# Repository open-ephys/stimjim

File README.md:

Stimjim - a flexible, precise, and inexpensive open-source stimulator
-------------------------------
Stimjim is a current and voltage stimulator for stimulating neural tissue (as with stimulating electrodes). 

# Specifications:

 - Two independently-controllable output channels, each with both current and voltage output modes
 - Output range in current mode: -3.33mA to +3.33mA. 
 - Output range in voltage mode: -15V to 15V.
 - Pulse width down to 0.02 ms (as configured with default firmware)
 - Compliance voltage is +-13.7V in current mode (+/-3.33uA output possible for resistances up to 4k, +-137uA possible for resistances up to 100k)
 - Powered by USB
 - Channels are isolated from power supply and from each other.
 - Onboard ADC measurement of actual output current or voltage
 
# Building your own Stimjim:

Here are the steps to build your very own Stimjim box. 

### Option 1: Assemble (solder components onto) the board yourself.

1. Order printed circuit boards (PCBs) for the [main board](./PCB/stimjimFabricationFiles_v0.181.zip) (4-layer, 129x79.5 mm, otherwise standard order parameters) and the [enclosure front and back panels](./PCB/stimjimPanelFabricationFiles_v0.18.zip) (1-layer, 2 designs, total size 140x71 mm) from [JLCPCB](https://jlcpcb.com/), [Seeedstudio](https://www.seeedstudio.com/fusion_pcb.html) or any other PCB manufacturer. Note that for the panels, the PCB manufacturer may alert you to the fact that there is no exposed copper. This is correct, there should be a copper layer entirely covered by soldermask.
2. Order [components](./stimjim_BOM.xlsx) (entirely from [Digikey](https://www.digikey.com/)).
3. Solder components onto the PCB, using the [schematic](./schematic.pdf) and [layout](./pcb.pdf) files for reference. This may take a few hours, depending on your soldering experience and capability. I typically use a pair of good tweezers, leaded solder paste, and a soldering iron, although a reflow oven also will work as well and may be easier.

### Option 2: Use [SeeedStudio's assembly service](https://www.seeedstudio.com/fusion_pcb.html). 
Recent estimate is about $800 for two assembled boards, plus another roughly $100 for the enclosure and panels. Thanks to Vincent Prevosto for trying this out and submitting these instructions!

1.  The main board PCB and components can be ordered and assembled together on SeeedStudio.
    To order assembled boards, go to [https://www.seeedstudio.com/fusion_pcb.html](https://www.seeedstudio.com/fusion_pcb.html).
   
    *   Click on **Add Gerber Files** and upload [the main board Gerber files](./PCB/stimjimFabricationFiles_v0.181.zip). 
        Make sure to select 4 layers and enter correct dimensions (129x79.5 mm). 
        Select PCB quantity (minimum 5).
    *   Move now to the **PCB Assembly** section.
    *   Click on **Add Assembly Drawing & Pick and Place File** and upload the [zip file containing pdf assembly files and position files](./PCB/stimjim_SeeedStudioAssembly_PickAndPlace.zip).
    *   Select the requested PCB assembly quantity (tested with 2 for $780 USD in late 2019).
    *   Click on **Add BOM File** and upload the [Seeedstudio-formatted Bill of Materials](./PCB/stimjim_SeeedStudioAssembly_BOM.xlsx). The service will check parts availability. Seeedstudio may not be able to provide an instant quote, but they should send you one within a day.
    *   Seeedstudio-assembled Stimjims have been successfully tested by one user, but you have the option to have SeeedStudio test the assembly as well.
   
2. Order the [front and back panels for the enclosure](./PCB/stimjimPanelFabricationFiles_v0.18.zip) (1-layer, 2 designs, total size 140x71 mm) from [Seeedstudio](https://www.seeedstudio.com/fusion_pcb.html), [JLCPCB](https://jlcpcb.com/) or any other PCB company you like.
3. Order the enclosure itself (see the line "enclosure" in the [Bill of materials](./stimjim_BOM.xlsx)) from [Digikey](https://www.digikey.com/).

### Continuing from either option 1 or 2:

4.  Put the main board inside the enclosure (bottom slot), and screw the panels onto the front and back of the enclosure. 
5.  Connect the Stimjim to the computer via USB. Compile and download the [firmware](./stimjimPulser/) onto the Teensy, using the [Arduino IDE](https://www.arduino.cc/en/main/software) with [Teensyduino](https://www.pjrc.com/teensy/td_download.html) installed (or write your own!). Before compiling stimjimPulser.ino, You will need to install the Stimjim library by copying the [stimjim library folder](./lib/) to the appropriate arduino "libraries" folder on your computer. On Windows, this is typically My Documents/Arduino/libraries and on linux it is typically ~/Arduino/libraries. 
6.  Upon bootup, Stimjim should self-report (via the serial connection, visible using the "Serial Monitor" tool in the Arduino IDE) on a handful of calibration routines it runs. Example output looks as follows:

	    Booting StimJim on Teensy 3.5!
	    Initializing inputs...
	    ADC offsets (+-2.5V): -11.030000, -11.150000
	    ADC offsets (+-10V): -10.220000, -10.340000
	    current offsets: 11, 8
	    voltage offsets: 0, 0
	    Ready to go!
	   
	The ADC offsets indicate the ADC reading (in ADC units, 2.4mV per ADC unit) from the output when the output is grounded, for channels 0 and 1, respectively. The ADC typically has a small but nonzero "Zero offset error" which is the reading when it should be reading exactly 0V. Stimjim measures this error (with two different range settings) and corrects all subsequent readings. We typically see values less than 20 - a value of +-4096 indicates some sort of problem with the board.
	
	Current offsets are the raw value of the DAC output (-32768 to 32767) that yields the current reading closest to 0uA. This offset is also used in subsequent stimulation to avoid any small but consistent DC current during pulses.

# Getting started using Stimjim:

To generate a pulse train, you first need to send a serial command, terminated by a newline (\n) in order to define a PulseTrain. An example command would be:

    S0,0,1,2000,1000000; 100,0,150; -100,-100,200
   
The "S" is to *s*pecify the parameters of a pulse train, and the zero immediately following the S implies that we are going to set parameters for PulseTrain 0. The code provided here allows Stimjim to store 100 different PulseTrain parameter sets. If any comma- and semicolon-separated numbers appear following the S, they are the pulse train parameters. A command that simply consists of "S0" will result in simply printing out the current parameters of PulseTrain 0. 

Once a PulseTrain is defined, to run it you would send a command of the form:

    T0

This tells Stimjim to start running PulseTrain 0. If we had parameterized PulseTrain #3, we could just as easily run PulseTrain #3 with the command "T3".

##  Parameterization 

The numbers that come after an "S" indicate parameters as denoted below:

1. [PulseTrain number], 
2. [output 0 mode],
3. [output 1 mode],
4. [period],
5. [duration];
6. [mV or uA for stage 0 output 0],
7. [mV or uA for stage 0 output 1],
8. [stage 0 duration (us)]; 
9. [mV or uA for stage 1 output 0],
10. [mV or uA for stage 1 output 1],
11. [stage 1 duration (us)];
12. (etc for additional stages, up to 10 total stages).

After the "S", the first parameter is the number of the PulseTrain that we are defining. The next two parameters are the modes of each output channels. Modes are as follows:

 - 0 = Voltage output
 - 1 = Current output
 - 2 = Output is disconnected
 - 3 = Output is grounded

Our example command above was: 
   
    S0,0,1,2000,1000000; 100,0,150; -100,-100,200
   
In this example, output 0 is generating a voltage output (mode 0), and output 1 is generating a current output (mode 1). To specify that a channel should not output anything during a pulse train, set the mode to 3 (ground).  

The fourth parameter is the _period_ of the pulse train. In this example, pulses are delivered every 2000 us (2 ms).

The fifth parameter is the _duration_ of the pulse train, in microseconds. In the example, the pulse train lasts for one second (1000000 microseconds).

Parameters after the 5th come in sets of 3, and describe a "stage" of a pulse in the train.  The first two parameters are the amplitude (in mV or uA, depending on whether the output is voltage or current) of each channel during that stage, and the third is the duration (in microseconds) of that stage. Note that a semi-colon is before the beginning of each set of 3, and the three parameters themselves are separated from each other by commas.

In the example given above, there are two stages to each pulse. In the first, channel 0 outputs 100mV, channel 1 outputs nothing, and that lasts for 150 usec. Then channel 0 switches to outputting -100mV, and channel 2 outputs -100uA for 200 usec. 

## Triggering
Stimjim can utilize trigger signals from its BNC inputs. To make a rising edge on input 0 trigger PulseTrain 1, send the command

	R0,1

To make a rising edge on input 1 trigger PulseTrain 2

	R1,2
	
And finally, to make a falling edge on input 1 trigger PulseTrain 2:

	R1,2,1

The final argument for the R command is optional, and defaults to 0 (rising edge).

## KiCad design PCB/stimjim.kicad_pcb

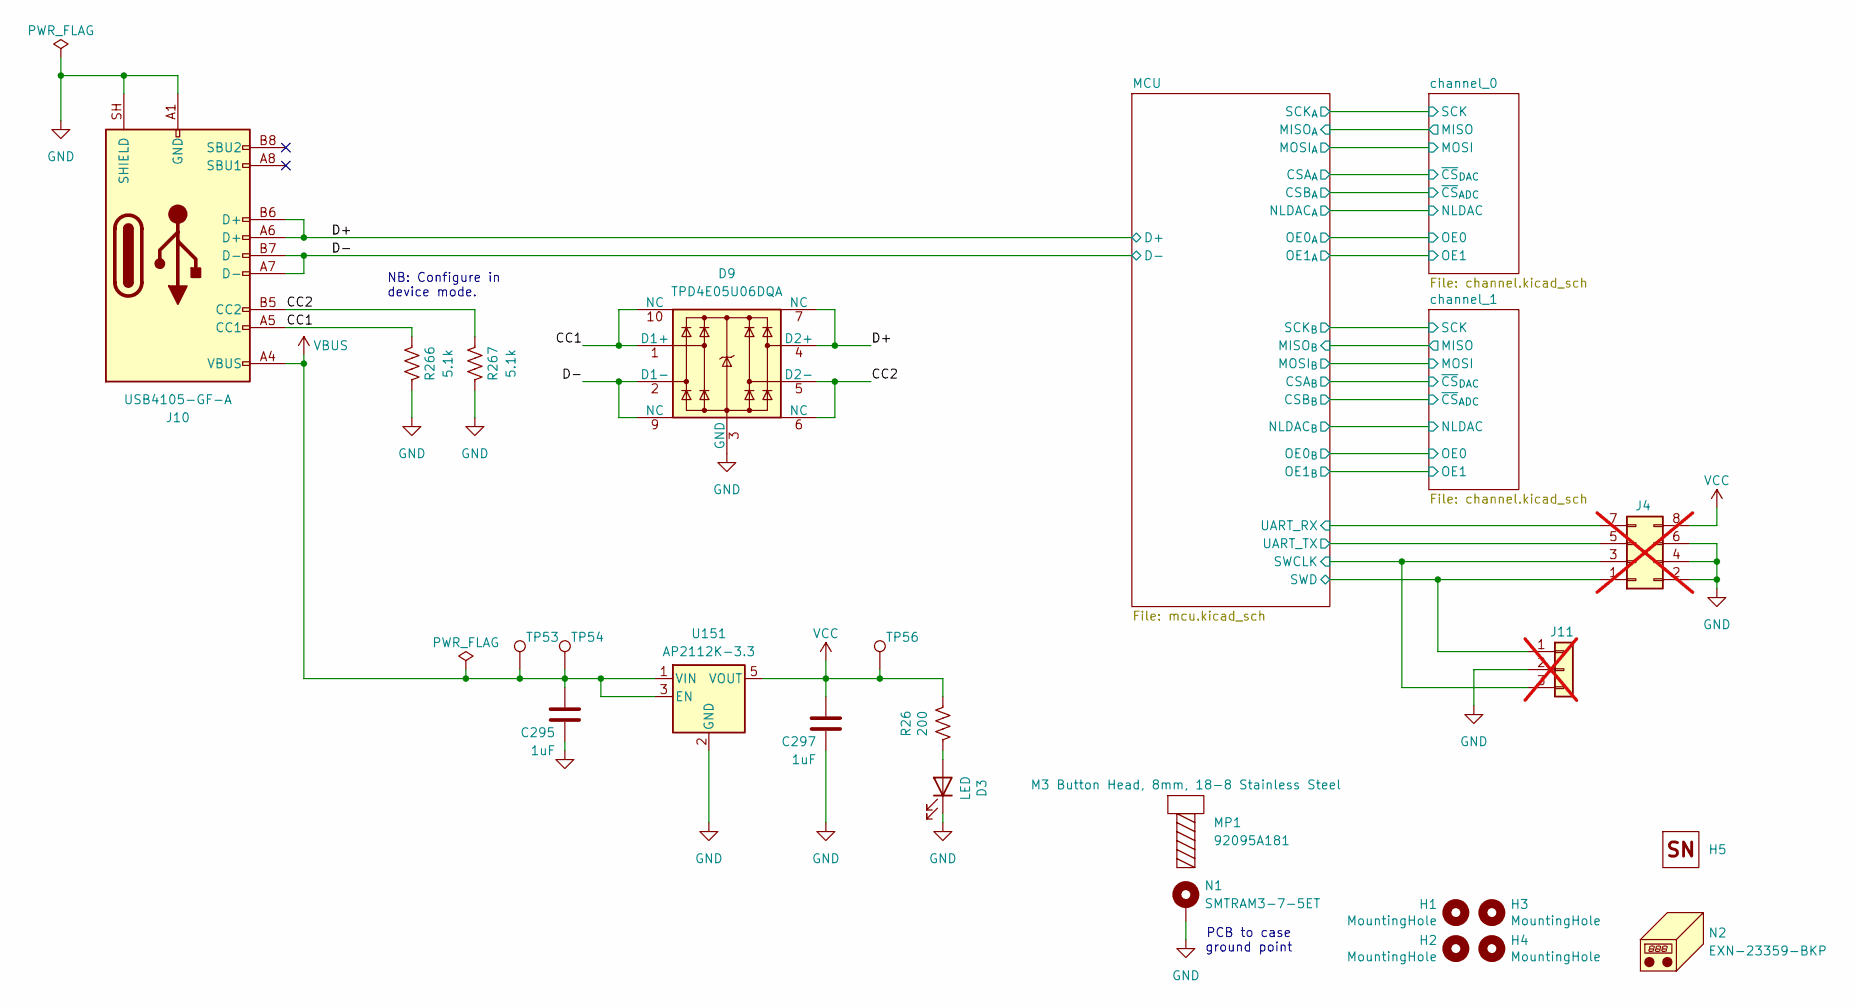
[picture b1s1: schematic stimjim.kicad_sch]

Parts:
C295, C297: 1uF; C_0603_1608Metric; Voltage 25V; MPN CL10A105KA8NNNC
D3: LED; LUMEX_SSF-LHXH100GD-01; MPN SSF-LXH100GD-01
D9: TPD4E05U06DQA; USON-10_2.5x1.0mm_P0.5mm; MPN TPD4E05U06DQAR
H1, H2, H3, H4: MountingHole; MountingHole_4.3mm_M4
H5: OEPS_SN-STICKER-8x20mm
J4: 10129383-910002ALF; PinHeader_2x04_P2.54mm_Vertical_SMD; MPN 10129383-910002ALF; not fitted
J10: USB4105-GF-A; USB_C_Receptacle_GCT_USB4105-xx-A_16P_TopMnt_Horizontal; MPN USB4105-GF-A
J11: BM03B-SRSS-TB; JST_SH_BM03B-SRSS-TB_1x03-1MP_P1.00mm_Vertical; MPN BM03B-SRSS-TB; not fitted
MP1: 92095A181
N1: SMTRAM3-7-5ET; SMTRA_M3-7-5ET; MPN SMTRAM3-7-5ET
N2: EXN-23359-BKP; MPN EXN-23359-SVP
R26: 200; R_0603_1608Metric; MPN RC0603FR-07200RL
R266, R267: 5.1k; R_0402_1005Metric; Tolerance 1%; MPN ERJ-2RKF5101X
TP53, TP54: GND; TestPoint_Pad_D2.0mm
TP56: VCC; TestPoint_Pad_D2.0mm
U151: AP2112K-3.3; SOT-23-5; MPN AP2112K-3.3TRG1

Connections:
/CC1: D9.1 (D1+), D9.10 (NC), J10.A5 (CC1), R266.1
/CC2: D9.5 (D2-), D9.6 (NC), J10.B5 (CC2), R267.1
/D+: D9.4 (D2+), D9.7 (NC), J10.A6 (D+), J10.B6 (D+); also elsewhere on the board
/D-: D9.2 (D1-), D9.9 (NC), J10.A7 (D-), J10.B7 (D-); also elsewhere on the board
/MCU/SWCLK: J4.3, J11.3; also elsewhere on the board
/MCU/SWD: J4.1, J11.1; also elsewhere on the board
/MCU/UART_RX: J4.7; also elsewhere on the board
/MCU/UART_TX: J4.5; also elsewhere on the board
GND: C295.2, C297.2, D3.1 (K), D9.3 (GND), D9.8 (GND), J4.2, J4.4, J4.6, J10.A1 (GND), J10.A12 (GND), J10.B1 (GND), J10.B12 (GND), J10.SH (SHIELD), J11.2, N1.1 (1_1), R266.2, R267.2, U151.2 (GND); also elsewhere on the board
unnamed: D3.2 (A), R26.2
VBUS: C295.1, J10.A4 (VBUS), J10.A9 (VBUS), J10.B4 (VBUS), J10.B9 (VBUS), TP53.1 (1_1), TP54.1 (1_1), U151.1 (VIN), U151.3 (EN); also elsewhere on the board
VCC: C297.1, J4.8, R26.1, TP56.1 (1_1), U151.5 (VOUT); also elsewhere on the board

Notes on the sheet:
NB: Configure in device mode.
PCB to case ground point

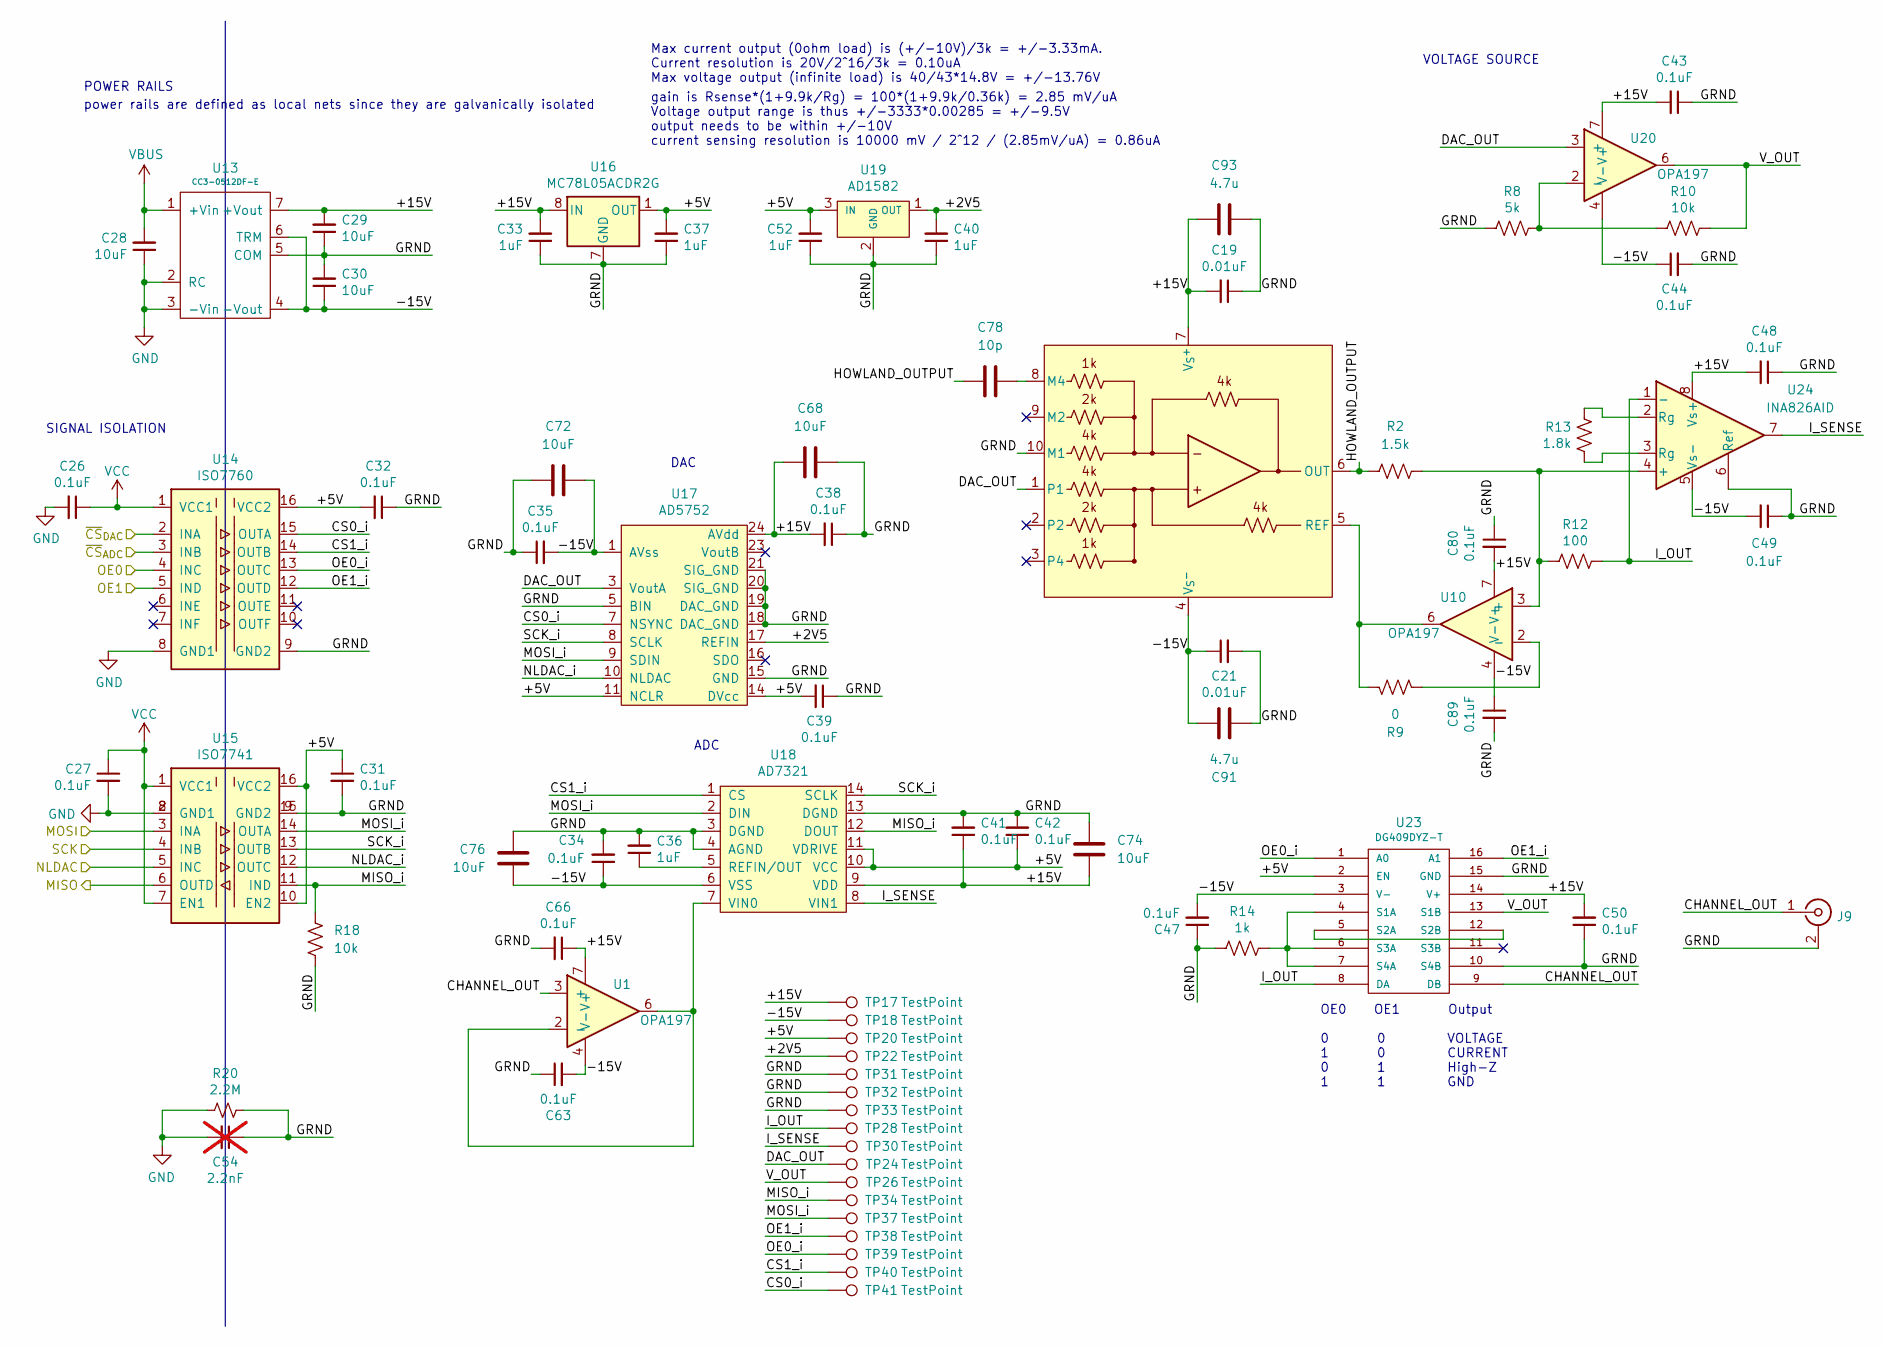
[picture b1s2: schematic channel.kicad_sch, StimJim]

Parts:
C19, C21: 0.01uF; C_0603_1608Metric; MPN C1608X7R1H103K080AA
C26, C27, C31, C32, C34, C35, C38, C39, C41, C42, C43, C44, C47, C48, C49, C50, C63, C66, C80, C89: 0.1uF; C_0603_1608Metric; MPN GRM188R72A104KA35D
C28, C29, C30: 10uF; C_1206_3216Metric_Pad1.33x1.80mm_HandSolder; Voltage 25V; MPN GRT319R6YA106KE01D
C33, C36, C37, C40, C52: 1uF; C_0603_1608Metric; Voltage 25V; MPN CL10A105KA8NNNC
C54: 2.2nF; C_1210_3225Metric_Pad1.33x2.70mm_HandSolder; MPN DNP; not fitted
C68, C72, C74, C76: 10uF; C_0603_1608Metric; MPN GRM188R6YA106MA73J
C78: 10p; C_0603_1608Metric; MPN C0603C100J5GACTU
C91, C93: 4.7u; C_0603_1608Metric; MPN GRM188R61E475KE11D
J9: 0731375003; BNC_Amphenol_B6252HB-NPP3G-50_Horizontal; MPN 0731375003
R2: 1.5k; R_0603_1608Metric; Tolerance 0.1%; MPN RG1608P-152-B-T5
R8: 5k; R_0603_1608Metric; Tolerance 0.1%; MPN RT0603BRE075KL
R9: 0; R_0603_1608Metric; MPN RCS06030000Z0EA
R10: 10k; R_0603_1608Metric; Tolerance 0.1%; MPN RG1608P-103-B-T5
R12: 100; R_0603_1608Metric; Tolerance 0.1%; MPN RG1608P-101-B-T5
R13: 1.8k; R_0603_1608Metric; Tolerance 0.1%; MPN RG1608P-182-B-T5
R14: 1k; R_0603_1608Metric; Tolerance 1%; MPN RG1608P-102-B-T5
R18: 10k; R_0603_1608Metric; MPN RC0603FR-0710KL
R20: 2.2M; R_1210_3225Metric_Pad1.30x2.65mm_HandSolder; MPN CRGCQ1210J2M2
TP17, TP18, TP20, TP22: TestPoint; TestPoint_THTPad_1.0x1.0mm_Drill0.5mm
TP24, TP26, TP28, TP30, TP31, TP32, TP33, TP34, TP37, TP38, TP39, TP40, TP41: TestPoint; TestPoint_THTPad_D1.0mm_Drill0.5mm
U1, U10, U20: OPA197; SOIC-8_3.9x4.9mm_P1.27mm; MPN OPA197IDR
U13: CC3-0512DF-E; MPN CC3-0512DF-E
U14: ISO7760; SOIC-16W_7.5x10.3mm_P1.27mm; MPN ISO7760DWR
U15: ISO7741; SOIC-16W_7.5x10.3mm_P1.27mm; MPN ISO7741DWR
U16: MC78L05ACDR2G; SOIC-8_3.9x4.9mm_P1.27mm; MPN MC78L05ACDR2G
U17: AD5752; TSSOP-24_4.4x7.8mm_P0.65mm; MPN AD5752AREZ
U18: AD7321; TSSOP-14_4.4x5mm_P0.65mm; MPN AD7321BRUZ-REEL7
U19: AD1582; SOT-23; MPN AD1582ARTZ-REEL7
U23: DG409DYZ-T; SO-16_3.9x9.9mm_P1.27mm; MPN DG409DYZ-T
U24: INA826AID; SOIC-8_3.9x4.9mm_P1.27mm; MPN INA826AIDR
U27: LT1995; MSOP-10_3x3mm_P0.5mm; MPN LT1995CMS#PBF

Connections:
/MCU/CSA_{A}: U14.2 (INA); also elsewhere on the board
/MCU/CSB_{A}: U14.3 (INB); also elsewhere on the board
/MCU/MISO_{A}: U15.6 (OUTD); also elsewhere on the board
/MCU/MOSI_{A}: U15.3 (INA); also elsewhere on the board
/MCU/NLDAC_{A}: U15.5 (INC); also elsewhere on the board
/MCU/OE0_{A}: U14.4 (INC); also elsewhere on the board
/MCU/OE1_{A}: U14.5 (IND); also elsewhere on the board
/MCU/SCK_{A}: U15.4 (INB); also elsewhere on the board
/channel_0/+2V5: C40.2, TP22.1 (1_1), U17.17 (REFIN), U19.1 (OUT)
/channel_0/+5V: C31.1, C32.2, C37.2, C39.2, C42.1, C52.2, TP20.1 (1_1), U14.16 (VCC2), U15.10 (EN2), U15.16 (VCC2), U16.1 (OUT), U17.11 (NCLR), U17.14 (DVcc), U18.10 (VCC), U18.11 (VDRIVE), U19.3 (IN), U23.2 (EN)
/channel_0/+15V: C19.2, C29.2, C33.2, C38.2, C41.1, C43.2, C48.2, C50.2, C66.1, C68.1, C74.1, C80.2, C93.2, TP17.1 (1_1), U1.7 (V+), U10.7 (V+), U13.7 (+Vout), U16.8 (IN), U17.24 (AVdd), U18.9 (VDD), U20.7 (V+), U23.14 (V+), U24.8 (Vs+), U27.7 (V_{S}^{+})
/channel_0/-15V: C21.1, C30.1, C34.1, C35.2, C44.1, C47.2, C49.2, C63.2, C72.2, C76.2, C89.1, C91.2, TP18.1 (1_1), U1.4 (V-), U10.4 (V-), U13.4 (-Vout), U13.6 (TRM), U17.1 (AVss), U18.6 (VSS), U20.4 (V-), U23.3 (V-), U24.5 (Vs-), U27.4 (V_{S}^{-})
/channel_0/CHANNEL_OUT: J9.1 (In), U1.3 (+), U23.9 (DB)
/channel_0/CS0_i: TP41.1 (1_1), U14.15 (OUTA), U17.7 (NSYNC)
/channel_0/CS1_i: TP40.1 (1_1), U14.14 (OUTB), U18.1 (CS)
/channel_0/DAC_OUT: TP24.1 (1_1), U17.3 (VoutA), U20.3 (+), U27.1
/channel_0/GRND: C19.1, C21.2, C29.1, C30.2, C31.2, C32.1, C33.1, C34.2, C35.1, C36.2, C37.1, C38.1, C39.1, C40.1, C41.2, C42.2, C43.1, C44.2, C47.1, C48.1, C49.1, C50.1, C52.1, C54.1, C63.1, C66.2, C68.2, C72.1, C74.2, C76.1, C80.1, C89.2, C91.1, C93.1, J9.2 (Ext), R8.1, R14.1, R18.1, R20.1, TP31.1 (1_1), TP32.1 (1_1), TP33.1 (1_1), U13.5 (COM), U14.9 (GND2), U15.9 (GND2), U15.15 (GND2), U16.2 (GND), U16.3 (GND), U16.6 (GND), U16.7 (GND), U17.5 (BIN), U17.15 (GND), U17.18 (DAC_GND), U17.19 (DAC_GND), U17.20 (SIG_GND), U17.21 (SIG_GND), U18.3 (DGND), U18.4 (AGND), U18.13 (DGND), U19.2 (GND), U23.10 (S4B), U23.15 (GND), U24.6 (Ref), U27.10 (M1)
/channel_0/HOWLAND_OUTPUT: C78.1, R2.1, U27.6 (OUT)
/channel_0/I_OUT: R12.2, TP28.1 (1_1), U23.8 (DA), U24.1 (-)
/channel_0/I_SENSE: TP30.1 (1_1), U18.8 (VIN1), U24.7
/channel_0/MISO_i: R18.2, TP34.1 (1_1), U15.11 (IND), U18.12 (DOUT)
/channel_0/MOSI_i: TP37.1 (1_1), U15.14 (OUTA), U17.9 (SDIN), U18.2 (DIN)
/channel_0/NLDAC_i: U15.12 (OUTC), U17.10 (NLDAC)
/channel_0/OE0_i: TP39.1 (1_1), U14.13 (OUTC), U23.1 (A0)
/channel_0/OE1_i: TP38.1 (1_1), U14.12 (OUTD), U23.16 (A1)
/channel_0/SCK_i: U15.13 (OUTB), U17.8 (SCLK), U18.14 (SCLK)
/channel_0/V_OUT: R10.2, TP26.1 (1_1), U20.6, U23.13 (S1B)
GND: C26.2, C27.2, C28.1, C54.2, R20.2, U13.2 (RC), U13.3 (-Vin), U14.8 (GND1), U15.2 (GND1), U15.8 (GND1); also elsewhere on the board
unnamed: R13.1, U24.3 (Rg)
unnamed: R13.2, U24.2 (Rg)
unnamed: U1.2 (-), U1.6, U18.7 (VIN0)
unnamed: R2.2, R12.1, U10.3 (+), U24.4 (+)
unnamed: R9.2, U10.2 (-)
unnamed: C36.1, U18.5 (REFIN/OUT)
unnamed: R8.2, R10.1, U20.2 (-)
unnamed: R14.2, U23.4 (S1A), U23.6 (S3A), U23.7 (S4A)
unnamed: U23.5 (S2A), U23.12 (S2B)
unnamed: C78.2, U27.8 (M4)
unnamed: R9.1, U10.6, U27.5 (REF)
VBUS: C28.2, U13.1 (+Vin); also elsewhere on the board
VCC: C26.1, C27.1, U14.1 (VCC1), U15.1 (VCC1), U15.7 (EN1); also elsewhere on the board

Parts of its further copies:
C1, C2, C6, C7, C9, C11, C13, C14, C16, C17, C18, C20, C22, C23, C24, C25, C65, C67, C82, C90: 0.1uF; C_0603_1608Metric; MPN GRM188R72A104KA35D
C3, C4, C5: 10uF; C_1206_3216Metric_Pad1.33x1.80mm_HandSolder; Voltage 25V; MPN GRT319R6YA106KE01D
C8, C10, C12, C15, C51: 1uF; C_0603_1608Metric; Voltage 25V; MPN CL10A105KA8NNNC
C45, C46: 0.01uF; C_0603_1608Metric; MPN C1608X7R1H103K080AA
C53: 2.2nF; C_1210_3225Metric_Pad1.33x2.70mm_HandSolder; MPN DNP; not fitted
C69, C73, C75, C77: 10uF; C_0603_1608Metric; MPN GRM188R6YA106MA73J
C79: 10p; C_0603_1608Metric; MPN C0603C100J5GACTU
C92, C94: 4.7u; C_0603_1608Metric; MPN GRM188R61E475KE11D
J7: 0731375003; BNC_Amphenol_B6252HB-NPP3G-50_Horizontal; MPN 0731375003
R1: 5k; R_0603_1608Metric; Tolerance 0.1%; MPN RT0603BRE075KL
R3: 10k; R_0603_1608Metric; Tolerance 0.1%; MPN RG1608P-103-B-T5
R4: 1.5k; R_0603_1608Metric; Tolerance 0.1%; MPN RG1608P-152-B-T5
R5: 100; R_0603_1608Metric; Tolerance 0.1%; MPN RG1608P-101-B-T5
R6: 1.8k; R_0603_1608Metric; Tolerance 0.1%; MPN RG1608P-182-B-T5
R7: 1k; R_0603_1608Metric; Tolerance 1%; MPN RG1608P-102-B-T5
R11: 0; R_0603_1608Metric; MPN RCS06030000Z0EA
R17: 10k; R_0603_1608Metric; MPN RC0603FR-0710KL
R19: 2.2M; R_1210_3225Metric_Pad1.30x2.65mm_HandSolder; MPN CRGCQ1210J2M2
TP15, TP16, TP19, TP21: TestPoint; TestPoint_THTPad_1.0x1.0mm_Drill0.5mm
TP23, TP25, TP27, TP29, TP42, TP43, TP44, TP45, TP48, TP49, TP50, TP51, TP52: TestPoint; TestPoint_THTPad_D1.0mm_Drill0.5mm
U2: CC3-0512DF-E; MPN CC3-0512DF-E
U3: ISO7760; SOIC-16W_7.5x10.3mm_P1.27mm; MPN ISO7760DWR
U4: ISO7741; SOIC-16W_7.5x10.3mm_P1.27mm; MPN ISO7741DWR
U5: MC78L05ACDR2G; SOIC-8_3.9x4.9mm_P1.27mm; MPN MC78L05ACDR2G
U6: AD5752; TSSOP-24_4.4x7.8mm_P0.65mm; MPN AD5752AREZ
U7: AD7321; TSSOP-14_4.4x5mm_P0.65mm; MPN AD7321BRUZ-REEL7
U8: AD1582; SOT-23; MPN AD1582ARTZ-REEL7
U9, U21, U26: OPA197; SOIC-8_3.9x4.9mm_P1.27mm; MPN OPA197IDR
U12: DG409DYZ-T; SO-16_3.9x9.9mm_P1.27mm; MPN DG409DYZ-T
U28: LT1995; MSOP-10_3x3mm_P0.5mm; MPN LT1995CMS#PBF
U29: INA826AID; SOIC-8_3.9x4.9mm_P1.27mm; MPN INA826AIDR

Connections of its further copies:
/MCU/CSA_{B}: U3.2 (INA); also elsewhere on the board
/MCU/CSB_{B}: U3.3 (INB); also elsewhere on the board
/MCU/MISO_{B}: U4.6 (OUTD); also elsewhere on the board
/MCU/MOSI_{B}: U4.3 (INA); also elsewhere on the board
/MCU/NLDAC_{B}: U4.5 (INC); also elsewhere on the board
/MCU/OE0_{B}: U3.4 (INC); also elsewhere on the board
/MCU/OE1_{B}: U3.5 (IND); also elsewhere on the board
/MCU/SCK_{B}: U4.4 (INB); also elsewhere on the board
/channel_1/+2V5: C15.2, TP21.1 (1_1), U6.17 (REFIN), U8.1 (OUT)
/channel_1/+5V: C6.1, C7.2, C12.2, C14.2, C17.1, C51.2, TP19.1 (1_1), U3.16 (VCC2), U4.10 (EN2), U4.16 (VCC2), U5.1 (OUT), U6.11 (NCLR), U6.14 (DVcc), U7.10 (VCC), U7.11 (VDRIVE), U8.3 (IN), U12.2 (EN)
/channel_1/+15V: C4.2, C8.2, C13.2, C16.1, C18.2, C23.2, C25.2, C45.2, C67.1, C69.1, C75.1, C82.2, C94.2, TP15.1 (1_1), U2.7 (+Vout), U5.8 (IN), U6.24 (AVdd), U7.9 (VDD), U9.7 (V+), U12.14 (V+), U21.7 (V+), U26.7 (V+), U28.7 (V_{S}^{+}), U29.8 (Vs+)
/channel_1/-15V: C5.1, C9.1, C11.2, C20.1, C22.2, C24.2, C46.1, C65.2, C73.2, C77.2, C90.1, C92.2, TP16.1 (1_1), U2.4 (-Vout), U2.6 (TRM), U6.1 (AVss), U7.6 (VSS), U9.4 (V-), U12.3 (V-), U21.4 (V-), U26.4 (V-), U28.4 (V_{S}^{-}), U29.5 (Vs-)
/channel_1/CHANNEL_OUT: J7.1 (In), U12.9 (DB), U26.3 (+)
/channel_1/CS0_i: TP52.1 (1_1), U3.15 (OUTA), U6.7 (NSYNC)
/channel_1/CS1_i: TP51.1 (1_1), U3.14 (OUTB), U7.1 (CS)
/channel_1/DAC_OUT: TP23.1 (1_1), U6.3 (VoutA), U9.3 (+), U28.1
/channel_1/GRND: C4.1, C5.2, C6.2, C7.1, C8.1, C9.2, C10.2, C11.1, C12.1, C13.1, C14.1, C15.1, C16.2, C17.2, C18.1, C20.2, C22.1, C23.1, C24.1, C25.1, C45.1, C46.2, C51.1, C53.1, C65.1, C67.2, C69.2, C73.1, C75.2, C77.1, C82.1, C90.2, C92.1, C94.1, J7.2 (Ext), R1.1, R7.1, R17.1, R19.1, TP42.1 (1_1), TP43.1 (1_1), TP44.1 (1_1), U2.5 (COM), U3.9 (GND2), U4.9 (GND2), U4.15 (GND2), U5.2 (GND), U5.3 (GND), U5.6 (GND), U5.7 (GND), U6.5 (BIN), U6.15 (GND), U6.18 (DAC_GND), U6.19 (DAC_GND), U6.20 (SIG_GND), U6.21 (SIG_GND), U7.3 (DGND), U7.4 (AGND), U7.13 (DGND), U8.2 (GND), U12.10 (S4B), U12.15 (GND), U28.10 (M1), U29.6 (Ref)
/channel_1/HOWLAND_OUTPUT: C79.1, R4.1, U28.6 (OUT)
/channel_1/I_OUT: R5.2, TP27.1 (1_1), U12.8 (DA), U29.1 (-)
/channel_1/I_SENSE: TP29.1 (1_1), U7.8 (VIN1), U29.7
/channel_1/MISO_i: R17.2, TP45.1 (1_1), U4.11 (IND), U7.12 (DOUT)
/channel_1/MOSI_i: TP48.1 (1_1), U4.14 (OUTA), U6.9 (SDIN), U7.2 (DIN)
/channel_1/NLDAC_i: U4.12 (OUTC), U6.10 (NLDAC)
/channel_1/OE0_i: TP50.1 (1_1), U3.13 (OUTC), U12.1 (A0)
/channel_1/OE1_i: TP49.1 (1_1), U3.12 (OUTD), U12.16 (A1)
/channel_1/SCK_i: U4.13 (OUTB), U6.8 (SCLK), U7.14 (SCLK)
/channel_1/V_OUT: R3.2, TP25.1 (1_1), U9.6, U12.13 (S1B)
GND: C1.2, C2.2, C3.1, C53.2, R19.2, U2.2 (RC), U2.3 (-Vin), U3.8 (GND1), U4.2 (GND1), U4.8 (GND1); also elsewhere on the board
unnamed: R6.1, U29.3 (Rg)
unnamed: R6.2, U29.2 (Rg)
unnamed: C10.1, U7.5 (REFIN/OUT)
unnamed: R1.2, R3.1, U9.2 (-)
unnamed: R7.2, U12.4 (S1A), U12.6 (S3A), U12.7 (S4A)
unnamed: U12.5 (S2A), U12.12 (S2B)
unnamed: R4.2, R5.1, U21.3 (+), U29.4 (+)
unnamed: R11.2, U21.2 (-)
unnamed: U7.7 (VIN0), U26.2 (-), U26.6
unnamed: C79.2, U28.8 (M4)
unnamed: R11.1, U21.6, U28.5 (REF)
VBUS: C3.2, U2.1 (+Vin); also elsewhere on the board
VCC: C1.1, C2.1, U3.1 (VCC1), U4.1 (VCC1), U4.7 (EN1); also elsewhere on the board

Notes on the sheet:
power rails are defined as local nets since they are galvanically isolated
ADC
gain is Rsense*(1+9.9k/Rg) = 100*(1+9.9k/0.36k) = 2.85 mV/uA Voltage output range is thus +/-3333*0.00285 = +/-9.5V output needs to be within +/-10V current sensing resolution is 10000 mV / 2^12 / (2.85mV/uA) = 0.86uA
OE0 OE1 Output 0 0 VOLTAGE 1 0 CURRENT 0 1 High-Z 1 1 GND
SIGNAL ISOLATION
POWER RAILS
VOLTAGE SOURCE
DAC
Max current output (0ohm load) is (+/-10V)/3k = +/-3.33mA. Current resolution is 20V/2^16/3k = 0.10uA Max voltage output (infinite load) is 40/43*14.8V = +/-13.76V

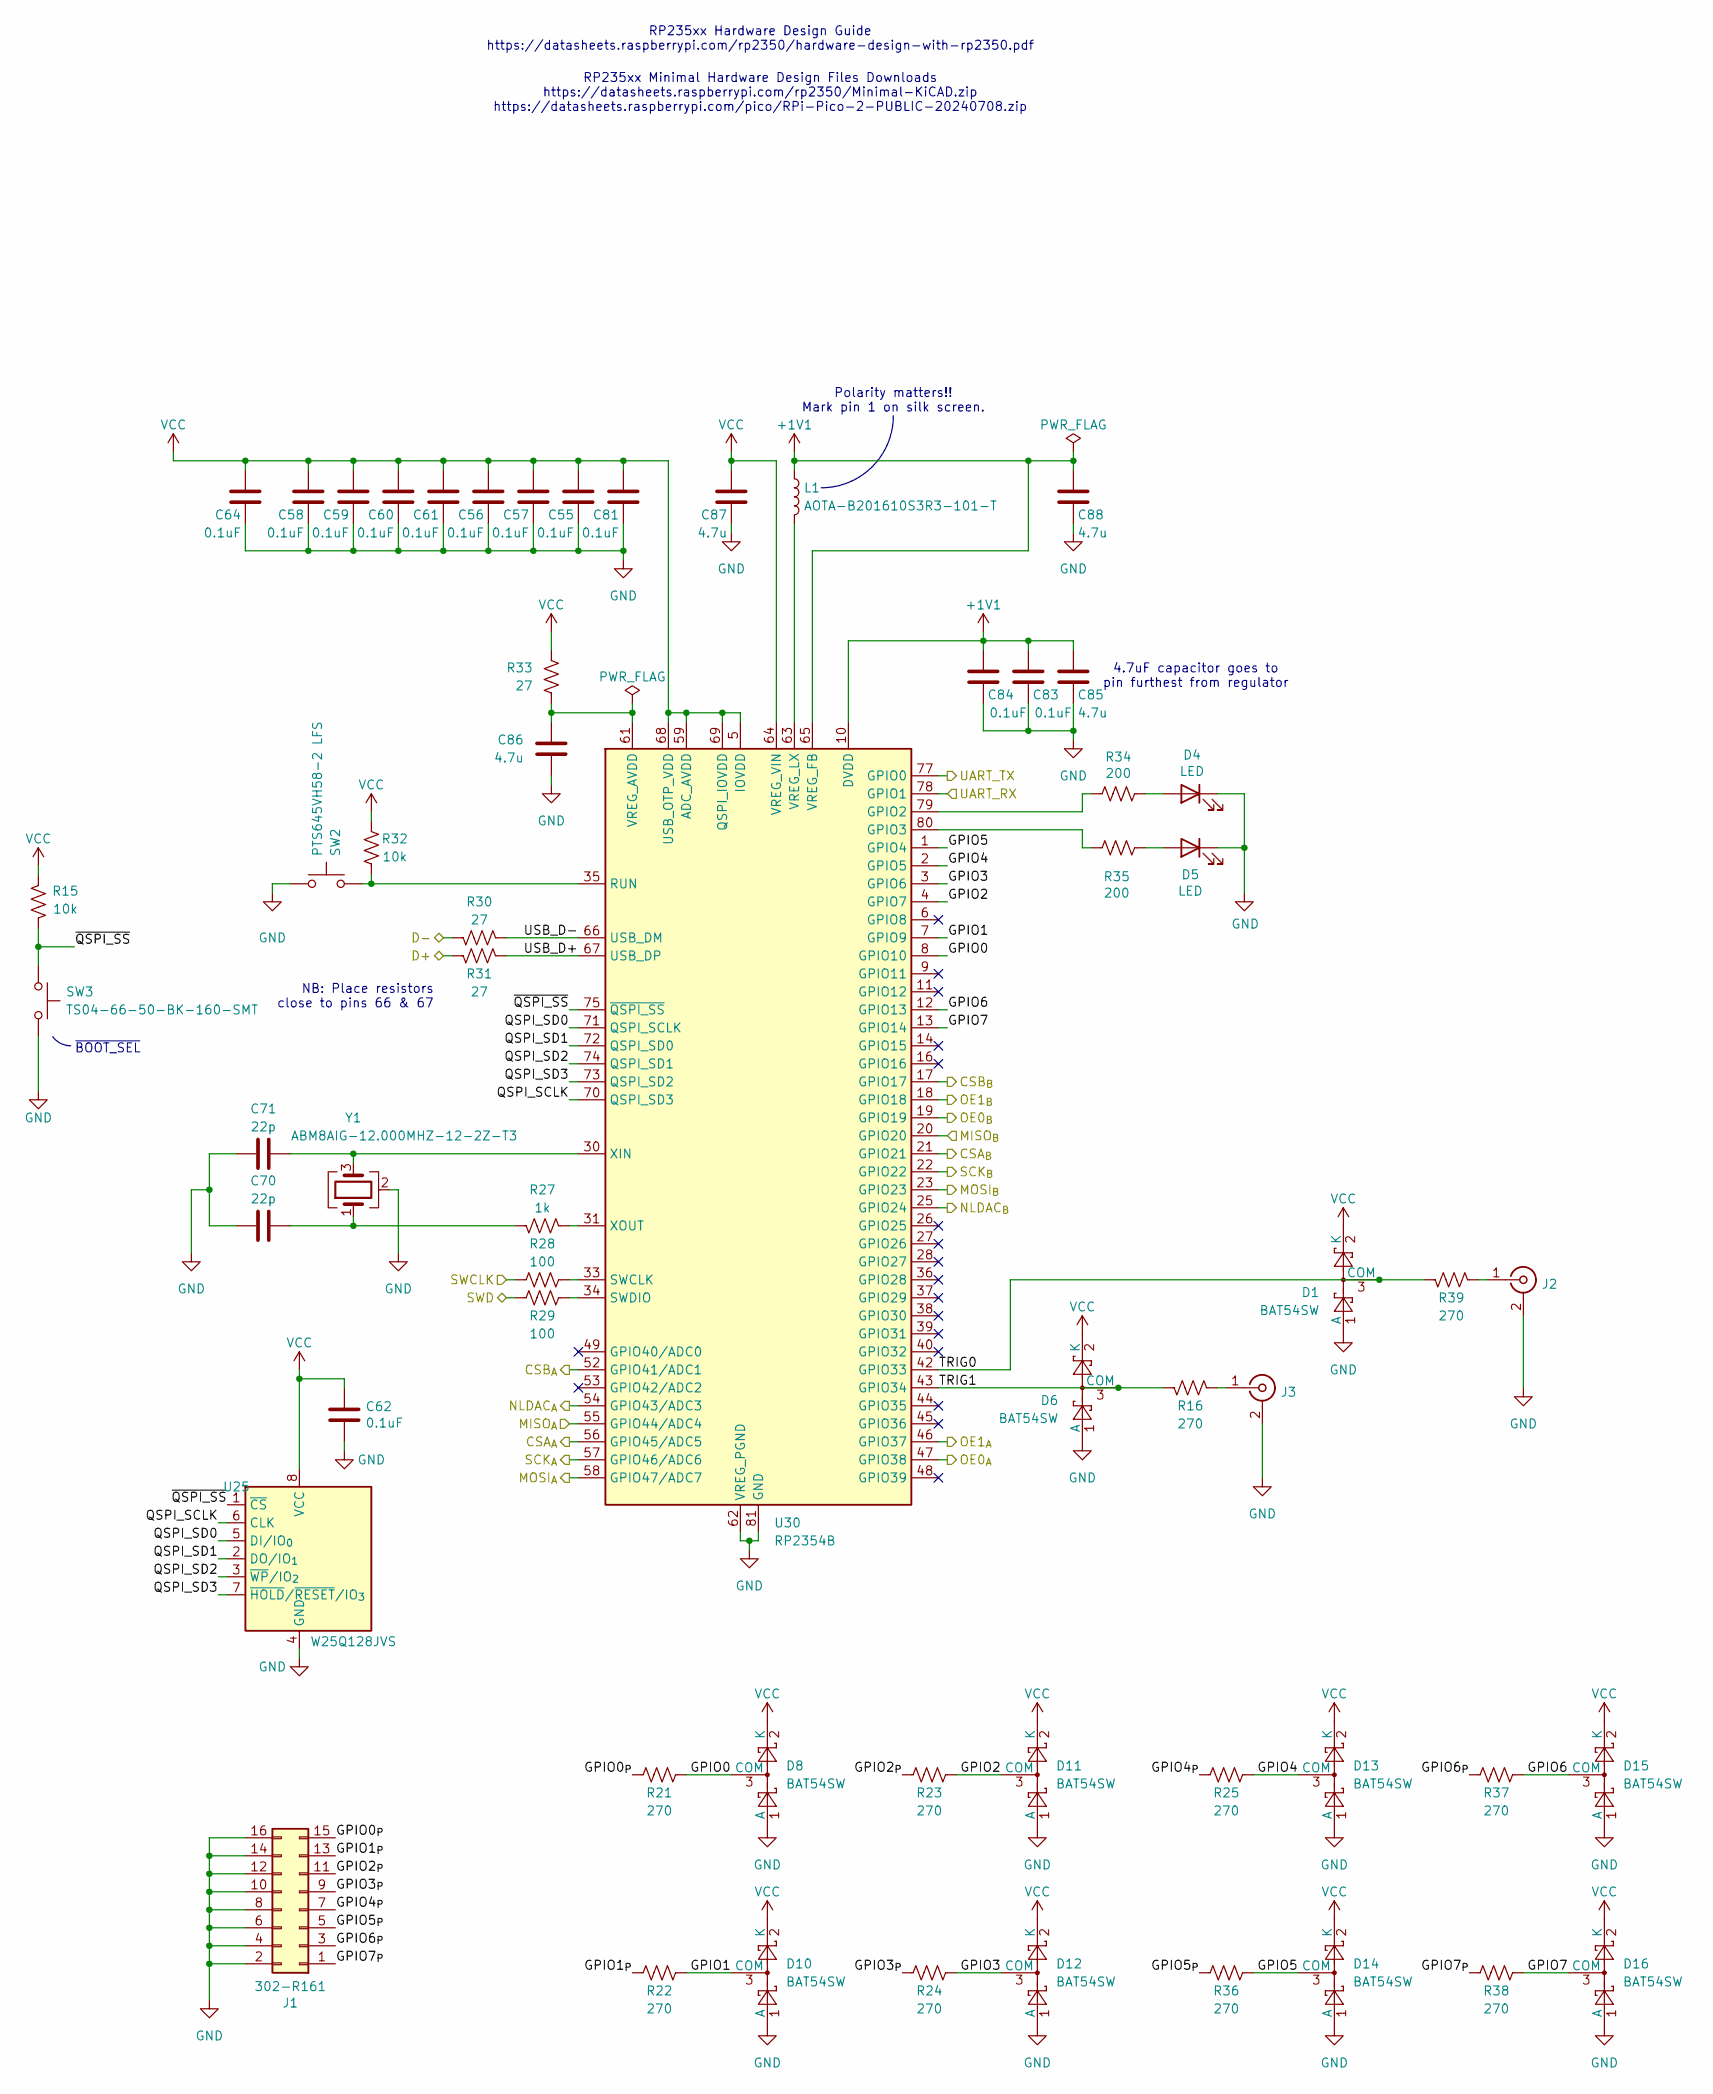
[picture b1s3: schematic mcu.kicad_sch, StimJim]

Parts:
C55, C56, C57, C58, C59, C60, C61, C62, C64, C81, C83, C84: 0.1uF; C_0402_1005Metric; MPN C1005X7R1E104K050BB
C70, C71: 22p; C_0402_1005Metric; MPN CL05C220JB51PNC
C85, C86, C87, C88: 4.7u; C_0402_1005Metric; Voltage 16V; MPN KGM05CR51C475MH
D1, D6, D8, D10, D11, D12, D13, D14, D15, D16: BAT54SW; SOT-323_SC-70; MPN BAT54SW
D4, D5: LED; LUMEX_SSF-LHXH100GD-01; MPN SSF-LXH100GD-01
J1: 302-R161; IDC-Header_2x08_P2.54mm_Horizontal; MPN 302-R161
J2, J3: 0731375003; BNC_Amphenol_B6252HB-NPP3G-50_Horizontal; MPN 0731375003
L1: AOTA-B201610S3R3-101-T; L_Abracon_2x1.6x1.0mm; MPN AOTA-B201610S3R3-101-T
R15, R32: 10k; R_0603_1608Metric; MPN RC0603FR-0710KL
R16, R21, R22, R23, R24, R25, R36, R37, R38, R39: 270; R_0805_2012Metric; MPN CRCW0805270RFKEAHP; LCSC C3013376
R27: 1k; R_0603_1608Metric; Tolerance 1%; MPN RG1608P-102-B-T5
R28, R29: 100; R_0603_1608Metric; Tolerance 1%; MPN CRCW0603100RFKEAHP
R30, R31, R33: 27; R_0402_1005Metric; MPN RMCF0402FT27R0
R34, R35: 200; R_0603_1608Metric; MPN RC0603FR-07200RL
SW2: PTS645VH58-2 LFS; SW_Tactile_SPST_Angled_PTS645Vx58-2LFS; MPN PTS645VH58-2 LFS
SW3: TS04-66-50-BK-160-SMT; SAMESKY_TS04-66-XX-BK-XXX-SMT-XX; MPN TS04-66-50-BK-160-SMT
U25: W25Q128JVS; SOIC-8_5.3x5.3mm_P1.27mm; MPN W25Q128JVSIQ
U30: RP2354B; QFN-80-1EP_10x10mm_P0.4mm_EP3.4x3.4mm; MPN SC1512-A4
Y1: ABM8AIG-12.000MHZ-12-2Z-T3; Crystal_SMD_Abracon_ABM8AIG-4Pin_3.2x2.5mm; MPN ABM8AIG-12.000MHZ-12-2Z-T3

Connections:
+1V1: C83.1, C84.1, C85.1, C88.1, L1.1, U30.10 (DVDD), U30.32 (DVDD), U30.51 (DVDD), U30.65 (VREG_FB)
/D+: R31.2; also elsewhere on the board
/D-: R30.2; also elsewhere on the board
/MCU/CSA_{A}: U30.56 (GPIO45/ADC5); also elsewhere on the board
/MCU/CSA_{B}: U30.21 (GPIO21); also elsewhere on the board
/MCU/CSB_{A}: U30.52 (GPIO41/ADC1); also elsewhere on the board
/MCU/CSB_{B}: U30.17 (GPIO17); also elsewhere on the board
/MCU/GPIO0: D8.3 (COM), R21.2, U30.8 (GPIO10)
/MCU/GPIO0_{P}: J1.15, R21.1
/MCU/GPIO1: D10.3 (COM), R22.2, U30.7 (GPIO9)
/MCU/GPIO1_{P}: J1.13, R22.1
/MCU/GPIO2: D11.3 (COM), R23.2, U30.4 (GPIO7)
/MCU/GPIO2_{P}: J1.11, R23.1
/MCU/GPIO3: D12.3 (COM), R24.2, U30.3 (GPIO6)
/MCU/GPIO3_{P}: J1.9, R24.1
/MCU/GPIO4: D13.3 (COM), R25.2, U30.2 (GPIO5)
/MCU/GPIO4_{P}: J1.7, R25.1
/MCU/GPIO5: D14.3 (COM), R36.2, U30.1 (GPIO4)
/MCU/GPIO5_{P}: J1.5, R36.1
/MCU/GPIO6: D15.3 (COM), R37.2, U30.12 (GPIO13)
/MCU/GPIO6_{P}: J1.3, R37.1
/MCU/GPIO7: D16.3 (COM), R38.2, U30.13 (GPIO14)
/MCU/GPIO7_{P}: J1.1, R38.1
/MCU/MISO_{A}: U30.55 (GPIO44/ADC4); also elsewhere on the board
/MCU/MISO_{B}: U30.20 (GPIO20); also elsewhere on the board
/MCU/MOSI_{A}: U30.58 (GPIO47/ADC7); also elsewhere on the board
/MCU/MOSI_{B}: U30.23 (GPIO23); also elsewhere on the board
/MCU/NLDAC_{A}: U30.54 (GPIO43/ADC3); also elsewhere on the board
/MCU/NLDAC_{B}: U30.25 (GPIO24); also elsewhere on the board
/MCU/OE0_{A}: U30.47 (GPIO38); also elsewhere on the board
/MCU/OE0_{B}: U30.19 (GPIO19); also elsewhere on the board
/MCU/OE1_{A}: U30.46 (GPIO37); also elsewhere on the board
/MCU/OE1_{B}: U30.18 (GPIO18); also elsewhere on the board
/MCU/QSPI_SCLK: U25.6 (CLK), U30.70 (QSPI_SD3)
/MCU/QSPI_SD0: U25.5 (DI/IO_{0}), U30.71 (QSPI_SCLK)
/MCU/QSPI_SD1: U25.2 (DO/IO_{1}), U30.72 (QSPI_SD0)
/MCU/QSPI_SD2: U25.3 (~WP/IO_{2}), U30.74 (QSPI_SD1)
/MCU/QSPI_SD3: U25.7 (~HOLD/~RESET/IO_{3}), U30.73 (QSPI_SD2)
/MCU/SCK_{A}: U30.57 (GPIO46/ADC6); also elsewhere on the board
/MCU/SCK_{B}: U30.22 (GPIO22); also elsewhere on the board
/MCU/SWCLK: R28.1; also elsewhere on the board
/MCU/SWD: R29.1; also elsewhere on the board
/MCU/TRIG0: D1.3 (COM), R39.2, U30.42 (GPIO33)
/MCU/TRIG1: D6.3 (COM), R16.2, U30.43 (GPIO34)
/MCU/UART_RX: U30.78 (GPIO1); also elsewhere on the board
/MCU/UART_TX: U30.77 (GPIO0); also elsewhere on the board
/MCU/USB_D+: R31.1, U30.67 (USB_DP)
/MCU/USB_D-: R30.1, U30.66 (USB_DM)
/MCU/~QSPI_SS: R15.2, SW3.2, U25.1 (~CS), U30.75 (~QSPI_SS)
GND: C55.2, C56.2, C57.2, C58.2, C59.2, C60.2, C61.2, C62.2, C64.2, C70.1, C71.1, C81.2, C83.2, C84.2, C85.2, C86.2, C87.2, C88.2, D1.1 (A), D4.1 (K), D5.1 (K), D6.1 (A), D8.1 (A), D10.1 (A), D11.1 (A), D12.1 (A), D13.1 (A), D14.1 (A), D15.1 (A), D16.1 (A), J1.2, J1.4, J1.6, J1.8, J1.10, J1.12, J1.14, J1.16, J2.2 (Ext), J3.2 (Ext), SW2.1, SW3.1, U25.4 (GND), U30.62 (VREG_PGND), U30.81 (GND), Y1.2 (G), Y1.4 (G); also elsewhere on the board
unnamed: C70.2, R27.2, Y1.1
unnamed: D4.2 (A), R34.1
unnamed: D5.2 (A), R35.1
unnamed: J2.1 (In), R39.1
unnamed: J3.1 (In), R16.1
unnamed: R34.2, U30.79 (GPIO2)
unnamed: R35.2, U30.80 (GPIO3)
unnamed: R32.2, SW2.2, U30.35 (RUN)
unnamed: R28.2, U30.33 (SWCLK)
unnamed: R29.2, U30.34 (SWDIO)
unnamed: C86.1, R33.2, U30.61 (VREG_AVDD)
unnamed: L1.2, U30.63 (VREG_LX)
unnamed: C71.2, U30.30 (XIN), Y1.3
unnamed: R27.1, U30.31 (XOUT)
VCC: C55.1, C56.1, C57.1, C58.1, C59.1, C60.1, C61.1, C62.1, C64.1, C81.1, C87.1, D1.2 (K), D6.2 (K), D8.2 (K), D10.2 (K), D11.2 (K), D12.2 (K), D13.2 (K), D14.2 (K), D15.2 (K), D16.2 (K), R15.1, R32.1, R33.1, U25.8 (VCC), U30.5 (IOVDD), U30.15 (IOVDD), U30.24 (IOVDD), U30.29 (IOVDD), U30.41 (IOVDD), U30.50 (IOVDD), U30.59 (ADC_AVDD), U30.60 (IOVDD), U30.64 (VREG_VIN), U30.68 (USB_OTP_VDD), U30.69 (QSPI_IOVDD), U30.76 (IOVDD); also elsewhere on the board

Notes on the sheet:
Polarity matters!! Mark pin 1 on silk screen.
RP235xx Minimal Hardware Design Files Downloads https://datasheets.raspberrypi.com/rp2350/Minimal-KiCAD.zip https://datasheets.raspberrypi.com/pico/RPi-Pico-2-PUBLIC-20240708.zip
~{BOOT_SEL}
NB: Place resistors close to pins 66 & 67
RP235xx Hardware Design Guide https://datasheets.raspberrypi.com/rp2350/hardware-design-with-rp2350.pdf
4.7uF capacitor goes to pin furthest from regulator
